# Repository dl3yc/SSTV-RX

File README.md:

SSTV-RX
=======

a reciever for SSTV on 2m ham radio band as software defined radio

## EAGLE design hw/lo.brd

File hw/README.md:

Hardware of SSTV-RX
=======

The hardware of the SSTV reciever consists of several modules. The combination of these modules gives a software defined radio.
TODO: block diagramm

Low Noise Amplifier(LNA)
======
MAX2634:
 - supply voltage(V): 2.2 .. 5.5
 - supply current(mA): 2.5(typ) .. 4
 - frequency range(MHz):  100 .. 600
 - noise figure(dB): 1.25(typ, 315MHz)
 - gain: 15.5dB(typ, 315MHz)

Preamplifier
======
MAX2614:
 - supply voltage(V): 3.0 .. 5.0(typ) .. 5.25
 - supply current(mA): 2.5(typ) .. 40.6
 - frequency range(MHz):  40 .. 4000
 - noise figure(dB): 2(typ) .. 2.95(2GHz)
 - gain: 18.6dB(typ, 1GHz)

I/Q demodulator
======
AD8348:
 - supply voltage(V): 2.7 .. 5.5
 - supply current(mA): 38 .. 48(typ) .. 58
 - LO frequency range(MHz): 100 .. 2000
 - RF frequency range(MHz): 50 .. 1000
 - LO input level(dBm): -12 .. -10(typ) .. 0
 - noise figure(dB): 9.4(150MHz)

PLL+VCO
======
ADF4360-9:
 - supply voltage(V): 3.0 .. 3.6
 - supply current(mA): 23 .. 30
 - frequency range(MHz): 65 .. 400
 - output power(dBm): -9 .. 0

SPI ADC
======
AD7352:
 - supply voltage(V): 2.25 .. 2.75(VDD)/3.6(VDRIVE)
 - supply current(mA): 10 .. 15
 - resolution: 12 bit
 - Signal to Noise Ratio(dB): 70(min) .. 71.5(typ) 
 - Spurious Free Dynamic Range (dB): -85(min) .. -78.5(typ)

Filter and Pads
======

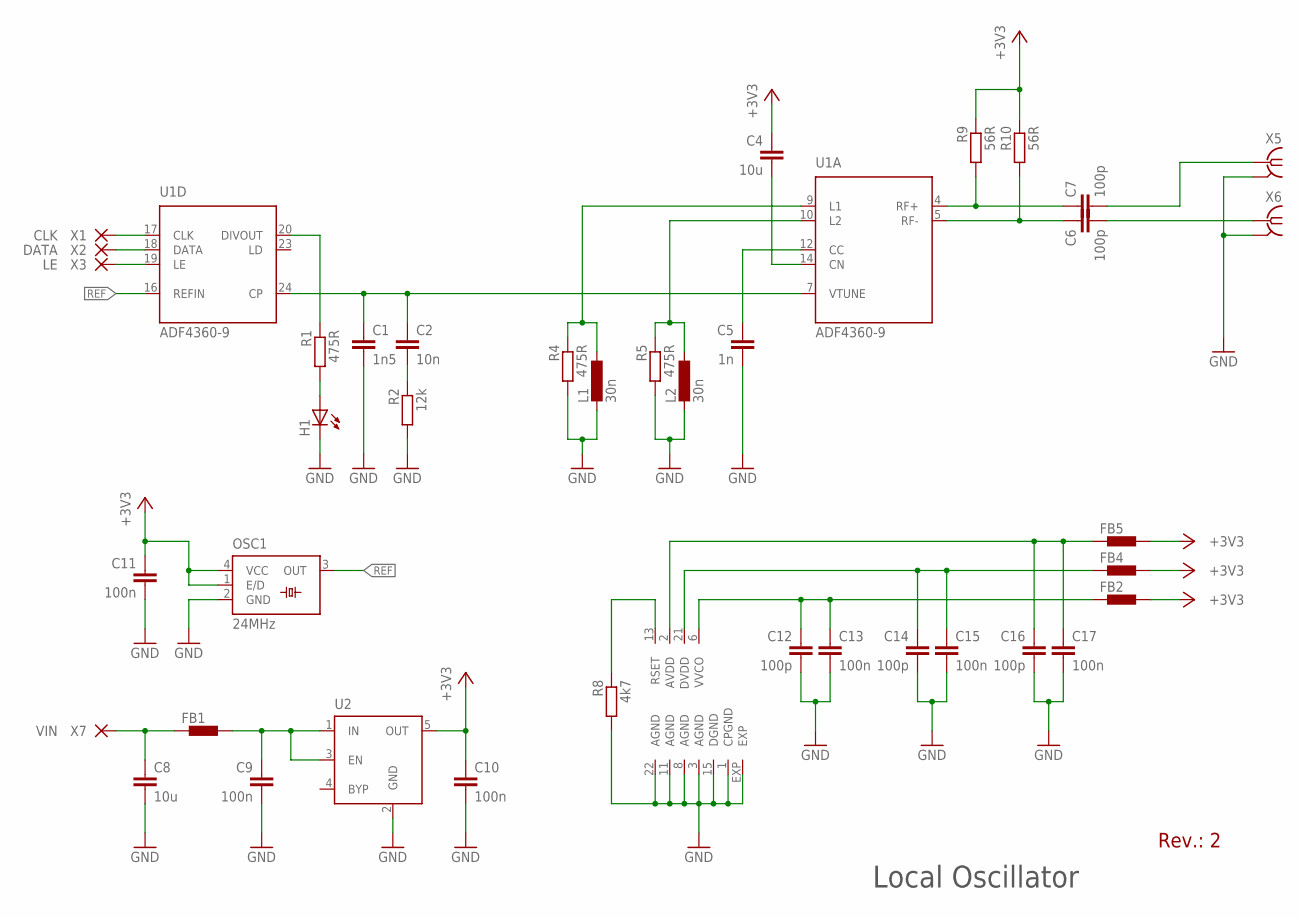
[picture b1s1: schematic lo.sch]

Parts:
C1: 1n5; C0402
C2: 10n; C0603
C4, C8: 10u; C0805
C5: 1n; C0603
C6, C7: 100p; C0402
C9, C10, C11, C13, C15, C17: 100n; C0603
C12, C14, C16: 100p; C0603
FB1, FB2, FB4, FB5: BML15H; R0603
H1: PL006-WCR13; SOT23
L1, L2: 30n; L2012C
OSC1: 24MHz; SM77H
R1: 475R; R1206
R2: 12k; R0603
R4, R5: 475R; R0603
R8: 4k7; R0603
R9, R10: 56R; R0603
U1: ADF4360-9; LFCSP24
U2: MIC5219XX; SOT23-5
X1: CLK; SMD1,27-2,54
X2: DATA; SMD1,27-2,54
X3: LE; SMD1,27-2,54
X5, X6: SMA-142-0701-881/886; J502-ND-142-0701-881/886
X7: VIN; SMD1,27-2,54

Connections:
+3V3: C4.1, C10.1, C11.1, FB2.2, FB4.2, FB5.2, OSC1.1 (E/D), OSC1.4 (VCC), R9.1, R10.1, U2.5 (OUT)
GND: C1.2, C5.2, C8.2, C9.2, C10.2, C11.2, C12.2, C13.2, C14.2, C15.2, C16.2, C17.2, H1.3 (C), L1.2, L2.2, OSC1.2 (GND), R2.2, R4.2, R5.2, R8.2, U1.1 (CPGND), U1.3 (AGND), U1.8 (AGND), U1.11 (AGND), U1.15 (DGND), U1.22 (AGND), U1.EXP, U2.2 (GND), X5.G@1 (GND), X5.G@2 (GND), X5.G@3 (GND), X5.G@4 (GND), X6.G@1 (GND), X6.G@2 (GND), X6.G@3 (GND), X6.G@4 (GND)
LD: C1.1, C2.1, U1.7 (VTUNE), U1.24 (CP)
unnamed: U1.17 (CLK), X1.1
unnamed: U1.18 (DATA), X2.1
unnamed: U1.19 (LE), X3.1
unnamed: C9.1, FB1.2, U2.1 (IN), U2.3 (EN)
unnamed: R1.1, U1.20 (DIVOUT)
unnamed: H1.1 (A), R1.2
unnamed: C2.2, R2.1
unnamed: C7.2, X5.1
unnamed: L2.1, R5.1, U1.10 (L2)
unnamed: C6.2, X6.1
unnamed: C5.1, U1.12 (CC)
unnamed: C8.1, FB1.1, X7.1
unnamed: C4.2, U1.14 (CN)
unnamed: C7.1, R9.2, U1.4 (RF+)
unnamed: C6.1, R10.2, U1.5 (RF-)
unnamed: R8.1, U1.13 (RSET)
unnamed: C12.1, C13.1, FB2.1, U1.6 (VVCO)
unnamed: C14.1, C15.1, FB4.1, U1.21 (DVDD)
unnamed: C16.1, C17.1, FB5.1, U1.2 (AVDD)
REF: OSC1.3 (OUT), U1.16 (REFIN)
RUT: L1.1, R4.1, U1.9 (L1)

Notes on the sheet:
Local Oscillator
Rev.: 2

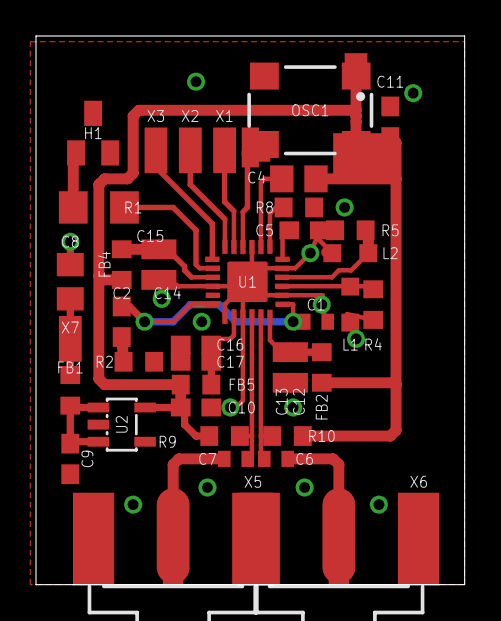
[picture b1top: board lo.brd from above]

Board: 2 copper layers, 23.8 x 30.5 mm, 39 parts (0 on the bottom side), 24 nets.

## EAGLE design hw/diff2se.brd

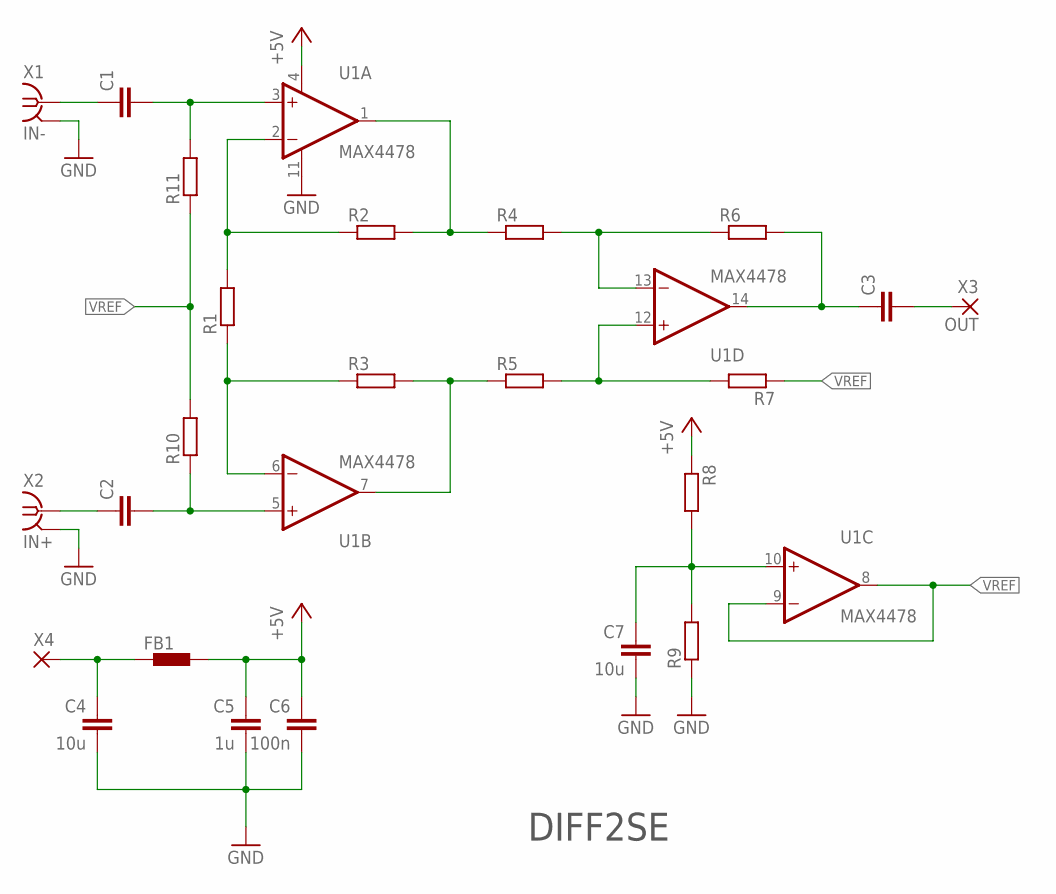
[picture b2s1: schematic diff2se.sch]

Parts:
C1, C2, C3: C-EUC0805K; C0805K
C4: 10u; C0805K
C5: 1u; C0805K
C6: 100n; C0805K
C7: 10u; C0402
FB1: BML15H; R0603
R1: R-EU_WSC01/2; WSC01/2
R2, R3, R4, R5, R6, R7: R-EU_R0805; R0805
R8, R9, R10, R11: R-EU_R0402; R0402
U1: MAX4478; SO14
X1: IN-; J502-ND-142-0701-881/886
X2: IN+; J502-ND-142-0701-881/886
X3: OUT; SMD1,27-2,54
X4: SMD2; SMD1,27-2,54

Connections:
+5V: C5.1, C6.1, FB1.2, R8.1, U1.4 (V+)
GND: C4.2, C5.2, C6.2, C7.2, R9.1, U1.11 (V-), X1.G@1 (GND), X1.G@2 (GND), X1.G@3 (GND), X1.G@4 (GND), X2.G@1 (GND), X2.G@2 (GND), X2.G@3 (GND), X2.G@4 (GND)
unnamed: R1.2, R2.1, U1.2 (-IN)
unnamed: R1.1, R3.1, U1.6 (-IN)
unnamed: R3.2, R5.1, U1.7 (OUT)
unnamed: R2.2, R4.1, U1.1 (OUT)
unnamed: C1.1, X1.1
unnamed: C1.2, R11.2, U1.3 (+IN)
unnamed: C2.1, X2.1
unnamed: C2.2, R10.1, U1.5 (+IN)
unnamed: R4.2, R6.1, U1.13 (-IN)
unnamed: R5.2, R7.2, U1.12 (+IN)
unnamed: C3.1, R6.2, U1.14 (OUT)
unnamed: C3.2, X3.1
unnamed: C4.1, FB1.1, X4.1
unnamed: C7.1, R8.2, R9.2, U1.10 (+IN)
VREF: R7.1, R10.2, R11.1, U1.8 (OUT), U1.9 (-IN)

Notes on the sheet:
DIFF2SE

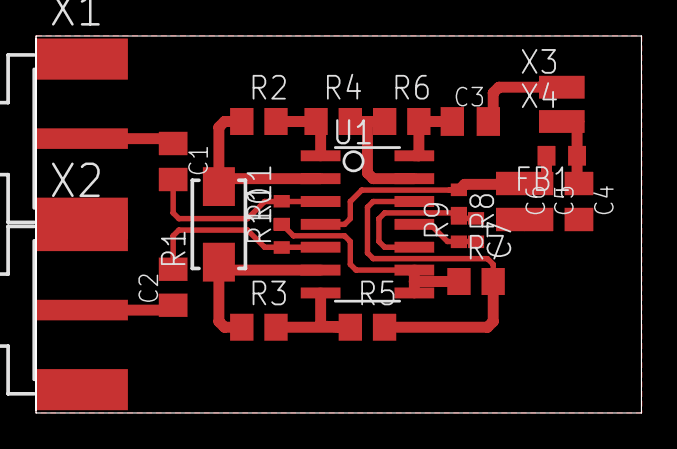
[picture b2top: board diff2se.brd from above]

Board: 2 copper layers, 33.6 x 20.9 mm, 24 parts (0 on the bottom side), 17 nets.

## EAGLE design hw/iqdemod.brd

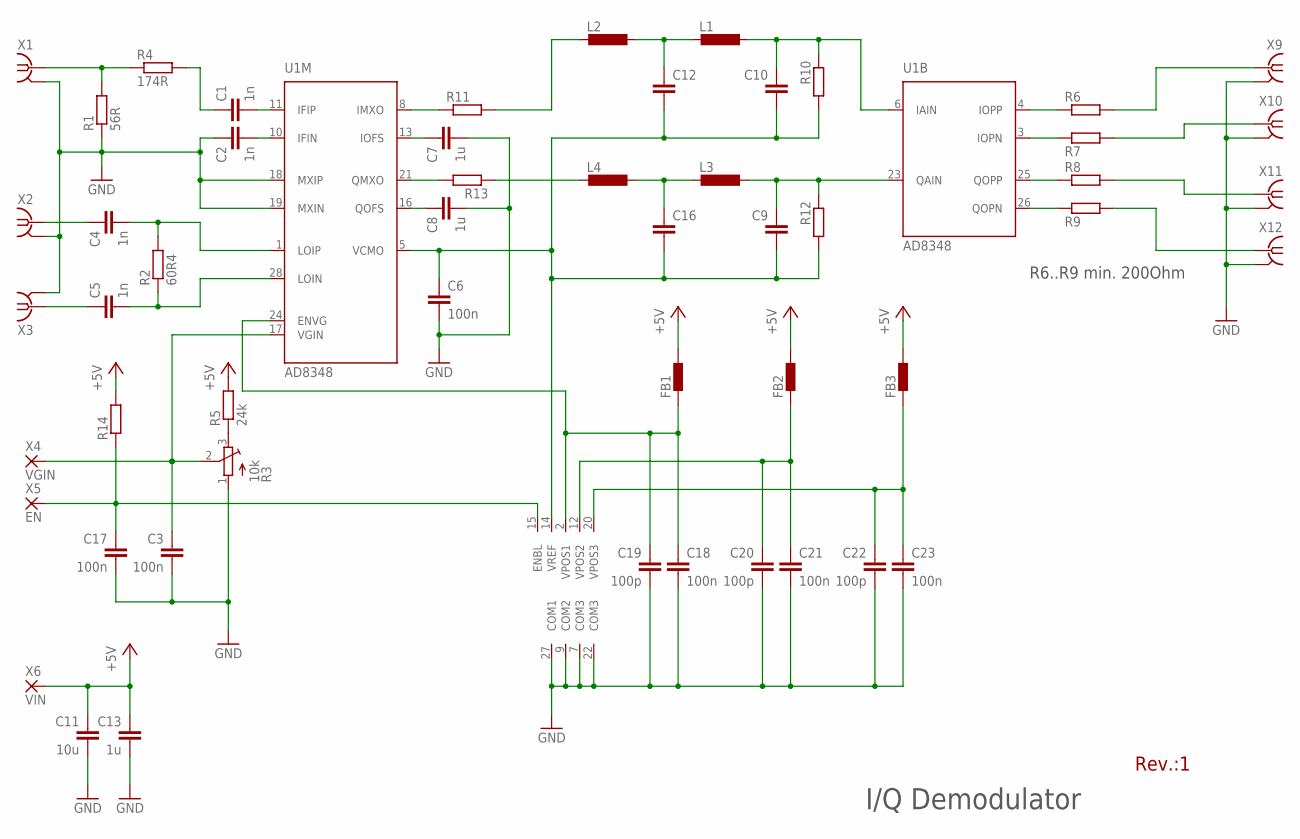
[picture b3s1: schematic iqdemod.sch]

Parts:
C1, C2, C4, C5: 1n; C0603
C3, C6, C17, C18, C21, C23: 100n; C0603
C7, C8, C13: 1u; C0603
C9, C10, C12, C16: C-EUC0603; C0603
C11: 10u; C0603
C19, C20, C22: 100p; C0603
FB1, FB2, FB3: BML15H; R0603
L1, L2, L3, L4: L-EUL2012C; L2012C
R1: 56R; R0603
R2: 60R4; R0603
R3: 10k; 3223J
R4: 174R; R0603
R5: 24k; R0603
R6, R7, R8, R9, R10, R11, R12, R13, R14: R-EU_R0603; R0603
U1: AD8348; TSSOP28
X1, X2, X3, X9, X10, X11, X12: SMA-142-0701-881/886; J502-ND-142-0701-881/886
X4: VGIN; SMD1,27-2,54
X5: EN; SMD1,27-2,54
X6: VIN; SMD1,27-2,54

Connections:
+5V: C11.1, C13.1, FB1.2, FB2.2, FB3.2, R5.2, R14.2, X6.1
GND: C2.1, C3.2, C6.2, C7.2, C8.2, C11.2, C13.2, C17.2, C18.2, C19.2, C20.2, C21.2, C22.2, C23.2, R1.1, R3.1 (A), U1.7 (COM3), U1.9 (COM2), U1.18 (MXIP), U1.19 (MXIN), U1.22 (COM3), U1.27 (COM1), X1.G@1 (2), X1.G@2 (2), X1.G@3 (2), X1.G@4 (2), X2.G@1 (2), X2.G@2 (2), X2.G@3 (2), X2.G@4 (2), X3.G@1 (2), X3.G@2 (2), X3.G@3 (2), X3.G@4 (2), X9.G@1 (2), X9.G@2 (2), X9.G@3 (2), X9.G@4 (2), X10.G@1 (2), X10.G@2 (2), X10.G@3 (2), X10.G@4 (2), X11.G@1 (2), X11.G@2 (2), X11.G@3 (2), X11.G@4 (2), X12.G@1 (2), X12.G@2 (2), X12.G@3 (2), X12.G@4 (2)
unnamed: C1.2, U1.11 (IFIP)
unnamed: C2.2, U1.10 (IFIN)
unnamed: R1.2, R4.1, X1.1
unnamed: C4.2, R2.2, U1.1 (LOIP)
unnamed: C5.2, R2.1, U1.28 (LOIN)
unnamed: C4.1, X2.1
unnamed: C3.1, R3.2 (S), U1.17 (VGIN), X4.1
unnamed: C5.1, X3.1
unnamed: C1.1, R4.2
unnamed: R3.3 (E), R5.1
unnamed: L2.2, R11.2
unnamed: L4.2, R13.1
unnamed: R6.1, U1.4 (IOPP)
unnamed: C8.1, U1.16 (QOFS)
unnamed: C7.1, U1.13 (IOFS)
unnamed: C12.1, L1.2, L2.1
unnamed: C10.1, L1.1, R10.1, U1.6 (IAIN)
unnamed: R7.1, U1.3 (IOPN)
unnamed: R8.1, U1.25 (QOPP)
unnamed: R9.1, U1.26 (QOPN)
unnamed: R6.2, X9.1
unnamed: R7.2, X10.1
unnamed: R8.2, X11.1
unnamed: R9.2, X12.1
unnamed: R11.1, U1.8 (IMXO)
unnamed: C17.1, R14.1, U1.15 (ENBL), X5.1
unnamed: C16.1, L3.2, L4.1
unnamed: C9.1, L3.1, R12.1, U1.23 (QAIN)
unnamed: R13.2, U1.21 (QMXO)
unnamed: C18.1, C19.1, FB1.1, U1.2 (VPOS1), U1.24 (ENVG)
unnamed: C20.1, C21.1, FB2.1, U1.12 (VPOS2)
unnamed: C22.1, C23.1, FB3.1, U1.20 (VPOS3)
VREF: C6.1, C9.2, C10.2, C12.2, C16.2, R10.2, R12.2, U1.5 (VCMO), U1.14 (VREF)

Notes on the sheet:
I/Q Demodulator
Rev.:1
R6..R9 min. 200Ohm

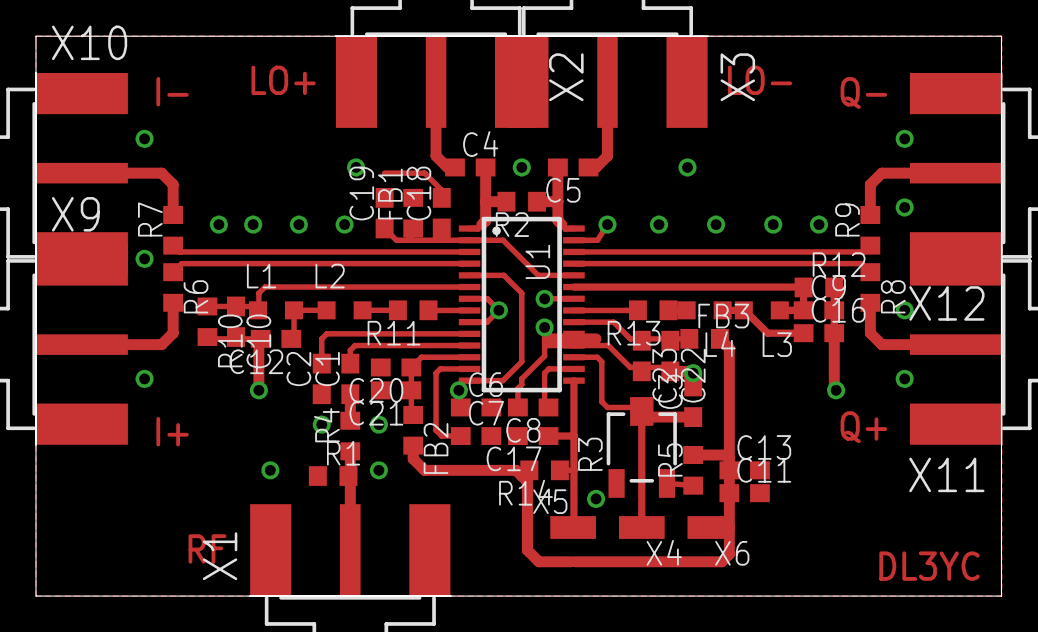
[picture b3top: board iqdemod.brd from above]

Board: 2 copper layers, 53.7 x 31.1 mm, 53 parts (0 on the bottom side), 35 nets.

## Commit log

2014-03-05 add datasheets for hw
2014-03-05 document lna, preamp, demod, vco
2014-03-05 add ad8348 eagle library
2014-03-05 ignore eagle temp files
2014-03-05 add ad7352 eagle library
2014-03-05 add adf4360 eagle library
2014-03-05 add max2614 eagle library
2014-03-05 add max2634 eagle library
2014-03-05 set meaningfull default names for submodules
2014-03-05 switch ENVG and VGIN to minimize crossing in schematic
2014-03-05 add ferrite bead eagle library
2014-03-05 first draft of i/q demodulator
2014-03-05 add simulation of i/q demodulator baseband filter
2014-03-05 ignore LTSpice temp files
2014-03-05 implement new baseband filter topology and add pad for supply
2014-03-05 simulate new filter topology(4th order lc filter)
2014-03-05 calculate values for baseband filter
2014-03-06 rev. 1: finished board
2014-03-06 add differential to single ended converter
2014-03-07 correct signal common to vref
2014-03-07 calculate vco parameters
2014-03-07 first draft of local oscillator
2014-03-07 simulate pll loop filter
    frequency range 288MHz - 292MHz
    channel spacing is 50kHz
    In-band Phase Noise is -93,7dBc/Hz
2014-03-07 simulate pll filter
2014-03-07 simulate adf4360
2014-03-07 use loop filter values from simulation
2014-03-08 make adf4360 footprint more comfortable to solder
2014-03-08 rev.1: finished lo board
2014-03-08 add rf signal chain simulation with ADISimRF
2014-03-09 add fxload as submodule for fx2programming
2014-03-09 move fxload to testset
2014-03-10 remove submodule fxload
2014-03-10 add testset
2014-03-10 document testset for local oscillator
2014-03-10 typo in heading
2014-03-10 calculate register content for lo
2014-03-10 optimize layout for easier soldering
2014-03-10 add savefile from AD ADF4360 Application
2014-03-10 add wiring info
2014-03-10 lo spectral measurments
